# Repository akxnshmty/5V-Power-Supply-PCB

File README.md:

# 5V Regulated Power Supply – PCB Design Project

This project is a simple and efficient 5V power supply board designed using **KiCad**. It uses the LM7805 voltage regulator to provide a steady 5V DC output from a higher DC input (e.g., 9V–12V adapter or battery).

## ⚙️ Features

- Provides regulated 5V output
- Input voltage range: 7V to 12V DC
- LED indicator for power status
- Designed and routed in KiCad
- Output via terminal block for easy connection

## 🧠 Learning Outcomes

- Understanding of voltage regulation using LM7805
- Schematic capture and PCB layout in KiCad
- Designing with basic components like resistors, capacitors, diodes, LEDs
- Generating Gerber files and PCB 3D visualization

## 📁 Files Included

- `.sch` – Schematic file
- `.kicad_pcb` – PCB layout file

## 🚀 Future Improvements

- Add USB output port
- Use switching regulator for better efficiency
- Include fuse or protection circuitry

## 📌 Notes

This project was completed as part of my early PCB design learning journey using KiCad. Feedback and suggestions are welcome!

---

Happy PCB Designing

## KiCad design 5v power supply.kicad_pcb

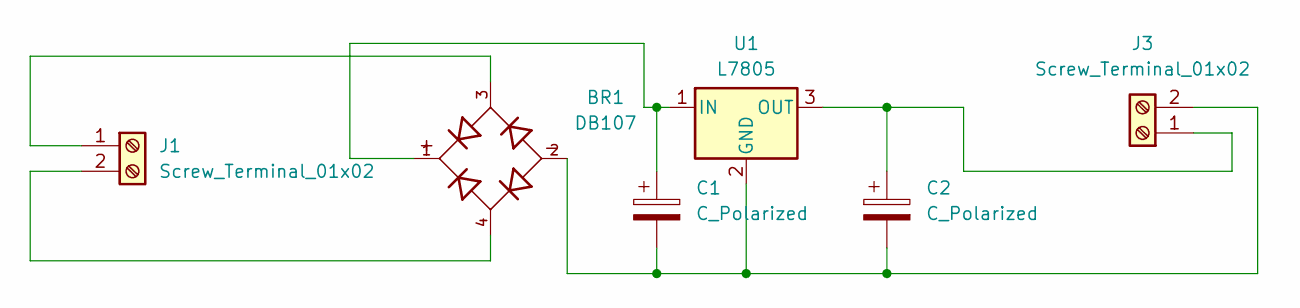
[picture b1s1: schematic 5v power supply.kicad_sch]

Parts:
BR1: DB107; DIP825W50P509L880H320Q4; PARTREV 13
C1, C2: C_Polarized; CP_Radial_D6.3mm_P2.50mm
J1: Screw_Terminal_01x02; TerminalBlock_Phoenix_MKDS-1,5-2_1x02_P5.00mm_Horizontal
J3: Screw_Terminal_01x02; TerminalBlock_Phoenix_MKDS-3-2-5.08_1x02_P5.08mm_Horizontal
U1: L7805; TO-220-3_Vertical

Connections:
unnamed: BR1.3, J1.1
unnamed: BR1.4, J1.2
unnamed: C2.1, J3.1, U1.3 (OUT)
unnamed: BR1.2, C1.2, C2.2, J3.2, U1.2 (GND)
unnamed: BR1.1, C1.1, U1.1 (IN)

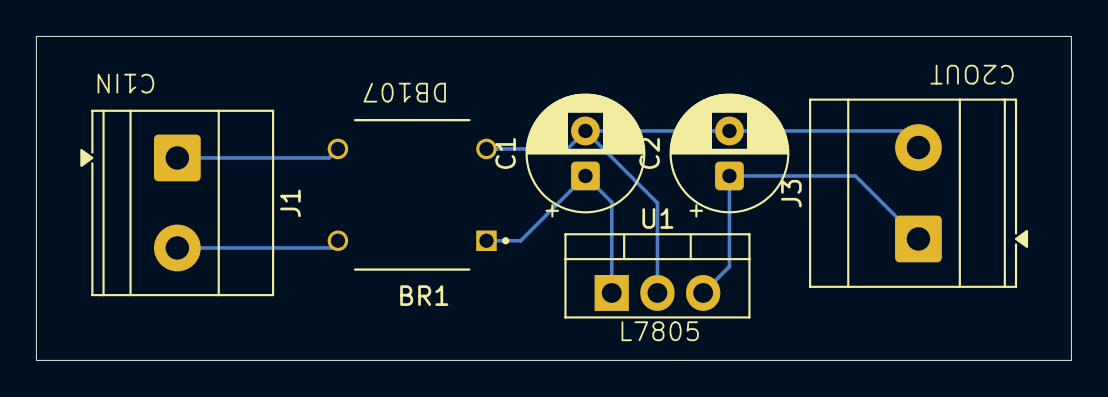
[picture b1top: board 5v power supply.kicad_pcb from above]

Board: 2 copper layers, 57.5 x 18.0 mm, 6 parts (0 on the bottom side), 5 nets.

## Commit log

2025-07-20 README.md
